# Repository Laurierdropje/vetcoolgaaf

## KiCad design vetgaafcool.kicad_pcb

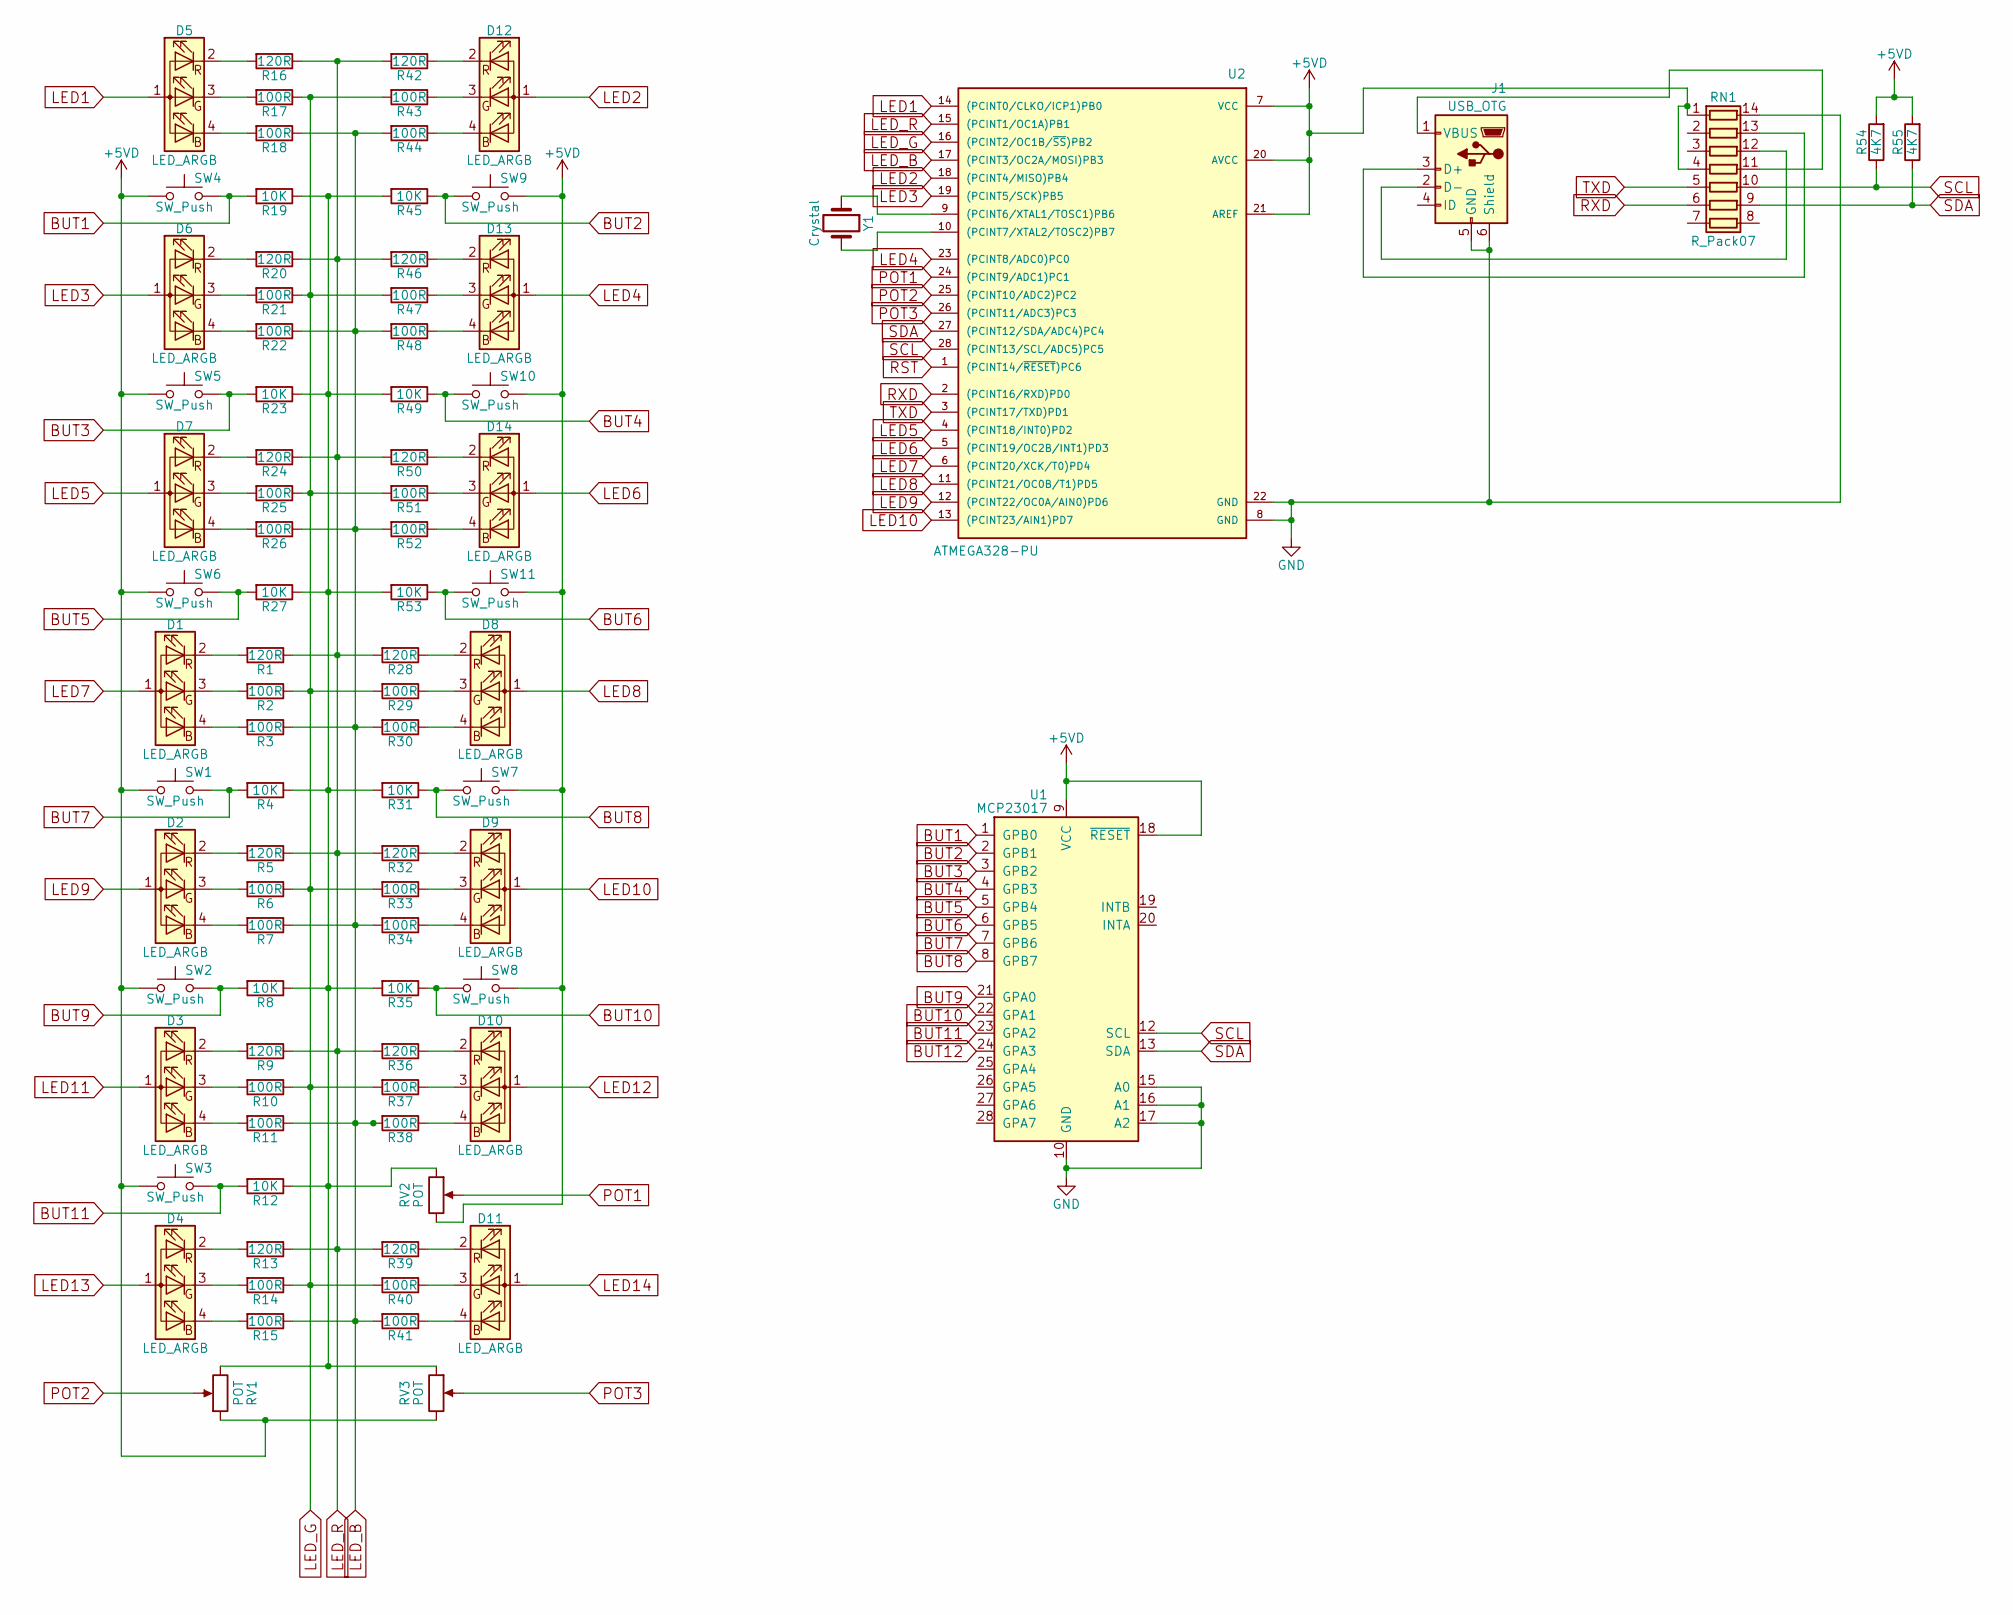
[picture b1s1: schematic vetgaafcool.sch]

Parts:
D1, D2, D3, D4, D5, D6, D7, D8, D9, D10, D11, D12, D13, D14: LED_ARGB; LED_RGB_PLCC-6
J1: USB_OTG; USB_Micro-B
R1, R5, R9, R13, R16, R20, R24, R28, R32, R36, R39, R42, R46, R50: 120R; R_Axial_DIN0207_L6.3mm_D2.5mm_P10.16mm_Horizontal
R2, R3, R6, R7, R10, R11, R14, R15, R17, R18, R21, R22, R25, R26, R29, R30, R33, R34, R37, R38, R40, R41, R43, R44, R47, R48, R51, R52: 100R; R_Axial_DIN0207_L6.3mm_D2.5mm_P10.16mm_Horizontal
R4, R8, R12, R19, R23, R27, R31, R35, R45, R49, R53: 10K; R_Axial_DIN0207_L6.3mm_D2.5mm_P10.16mm_Horizontal
R54, R55: 4K7; R_Axial_DIN0207_L6.3mm_D2.5mm_P10.16mm_Horizontal
RN1: R_Pack07; DIP-14_W7.62mm_Socket_LongPads
RV1, RV2, RV3: POT; Potentiometer_Alps_RK09Y_Vertical
SW1, SW2, SW3, SW4, SW5, SW6, SW7, SW8, SW9, SW10, SW11: SW_Push; SW_PUSH_6mm
U1: MCP23017; DIP-28_W7.62mm_Socket_LongPads
U2: ATMEGA328-PU; DIP-28_W7.62mm_Socket_LongPads
Y1: Crystal; Crystal_DS15_d1.5mm_l5.0mm_Vertical

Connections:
+5VD: R54.2, R55.2, RN1.1 (R1.1), RN1.4 (R4.1), RV1.1, RV2.3, RV3.3, SW1.1, SW2.1, SW3.1, SW4.1, SW5.1, SW6.1, SW7.2, SW8.2, SW9.2, SW10.2, SW11.2, U1.9 (VCC), U1.18 (~RESET), U2.7 (VCC), U2.20 (AVCC), U2.21 (AREF)
BUT1: R19.2, SW4.2, U1.1 (GPB0)
BUT2: R45.1, SW9.1, U1.2 (GPB1)
BUT3: R23.2, SW5.2, U1.3 (GPB2)
BUT4: R49.1, SW10.1, U1.4 (GPB3)
BUT5: R27.2, SW6.2, U1.5 (GPB4)
BUT6: R53.1, SW11.1, U1.6 (GPB5)
BUT7: R4.2, SW1.2, U1.7 (GPB6)
BUT8: R31.1, SW7.1, U1.8 (GPB7)
BUT9: R8.2, SW2.2, U1.21 (GPA0)
BUT10: R35.1, SW8.1, U1.22 (GPA1)
BUT11: R12.2, SW3.2, U1.23 (GPA2)
BUT12: U1.24 (GPA3)
GND: J1.5 (GND), J1.6 (Shield), RN1.14 (R1.2), U1.10 (GND), U1.15 (A0), U1.16 (A1), U1.17 (A2), U2.8 (GND), U2.22 (GND)
LED1: D5.1 (A), U2.14 ((PCINT0/CLKO/ICP1)PB0)
LED2: D12.1 (A), U2.18 ((PCINT4/MISO)PB4)
LED3: D6.1 (A), U2.19 ((PCINT5/SCK)PB5)
LED4: D13.1 (A), U2.23 ((PCINT8/ADC0)PC0)
LED5: D7.1 (A), U2.4 ((PCINT18/INT0)PD2)
LED6: D14.1 (A), U2.5 ((PCINT19/OC2B/INT1)PD3)
LED7: D1.1 (A), U2.6 ((PCINT20/XCK/T0)PD4)
LED8: D8.1 (A), U2.11 ((PCINT21/OC0B/T1)PD5)
LED9: D2.1 (A), U2.12 ((PCINT22/OC0A/AIN0)PD6)
LED10: D9.1 (A), U2.13 ((PCINT23/AIN1)PD7)
LED11: D3.1 (A)
LED12: D10.1 (A)
LED13: D4.1 (A)
LED14: D11.1 (A)
LED_B: R3.1, R7.1, R11.1, R15.1, R18.1, R22.1, R26.1, R30.2, R34.2, R38.2, R41.2, R44.2, R48.2, R52.2, U2.17 ((PCINT3/OC2A/MOSI)PB3)
LED_G: R2.1, R6.1, R10.1, R14.1, R17.1, R21.1, R25.1, R29.2, R33.2, R37.2, R40.2, R43.2, R47.2, R51.2, U2.16 ((PCINT2/OC1B/~SS~)PB2)
LED_R: R1.1, R5.1, R9.1, R13.1, R16.1, R20.1, R24.1, R28.2, R32.2, R36.2, R39.2, R42.2, R46.2, R50.2, U2.15 ((PCINT1/OC1A)PB1)
unnamed: D1.2 (RK), R1.2
unnamed: D1.3 (GK), R2.2
unnamed: D1.4 (BK), R3.2
unnamed: D2.2 (RK), R5.2
unnamed: D2.3 (GK), R6.2
unnamed: D2.4 (BK), R7.2
unnamed: D3.2 (RK), R9.2
unnamed: D3.3 (GK), R10.2
unnamed: D3.4 (BK), R11.2
unnamed: D4.2 (RK), R13.2
unnamed: D4.3 (GK), R14.2
unnamed: D4.4 (BK), R15.2
unnamed: D5.2 (RK), R16.2
unnamed: D5.3 (GK), R17.2
unnamed: D5.4 (BK), R18.2
unnamed: D6.2 (RK), R20.2
unnamed: D6.3 (GK), R21.2
unnamed: D6.4 (BK), R22.2
unnamed: D7.2 (RK), R24.2
unnamed: D7.3 (GK), R25.2
unnamed: D7.4 (BK), R26.2
unnamed: D8.2 (RK), R28.1
unnamed: D8.3 (GK), R29.1
unnamed: D8.4 (BK), R30.1
unnamed: D9.2 (RK), R32.1
unnamed: D9.3 (GK), R33.1
unnamed: D9.4 (BK), R34.1
unnamed: D10.2 (RK), R36.1
unnamed: D10.3 (GK), R37.1
unnamed: D10.4 (BK), R38.1
unnamed: D11.2 (RK), R39.1
unnamed: D11.3 (GK), R40.1
unnamed: D11.4 (BK), R41.1
unnamed: D12.2 (RK), R42.1
unnamed: D12.3 (GK), R43.1
unnamed: D12.4 (BK), R44.1
unnamed: D13.2 (RK), R46.1
unnamed: D13.3 (GK), R47.1
unnamed: D13.4 (BK), R48.1
unnamed: D14.2 (RK), R50.1
unnamed: D14.3 (GK), R51.1
unnamed: D14.4 (BK), R52.1
unnamed: J1.1 (VBUS), RN1.11 (R4.2)
unnamed: J1.2 (D-), RN1.12 (R3.2)
unnamed: J1.3 (D+), RN1.13 (R2.2)
unnamed: R4.1, R8.1, R12.1, R19.1, R23.1, R27.1, R31.2, R35.2, R45.2, R49.2, R53.2, RV1.3, RV2.1, RV3.1
unnamed: U2.9 ((PCINT6/XTAL1/TOSC1)PB6), Y1.1
unnamed: U2.10 ((PCINT7/XTAL2/TOSC2)PB7), Y1.2
POT1: RV2.2, U2.24 ((PCINT9/ADC1)PC1)
POT2: RV1.2, U2.25 ((PCINT10/ADC2)PC2)
POT3: RV3.2, U2.26 ((PCINT11/ADC3)PC3)
RST: U2.1 ((PCINT14/~RESET~)PC6)
RXD: RN1.6 (R6.1), U2.2 ((PCINT16/RXD)PD0)
SCL: R54.1, RN1.10 (R5.2), U1.12 (SCL), U2.28 ((PCINT13/SCL/ADC5)PC5)
SDA: R55.1, RN1.9 (R6.2), U1.13 (SDA), U2.27 ((PCINT12/SDA/ADC4)PC4)
TXD: RN1.5 (R5.1), U2.3 ((PCINT17/TXD)PD1)

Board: 2 copper layers, 88 parts (0 on the bottom side), 81 nets, no tracks yet.

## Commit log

2017-03-20 :tada: Added .gitattributes & .gitignore files
2017-03-20 jeej
    jeeeeeyjjj
